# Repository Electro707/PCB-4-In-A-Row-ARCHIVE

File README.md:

# PCB Digital 4-In-A-Row - ARCHIVED

This a PCB is a soldering kit for a 4-In-A-Row game. This specific repo is archived. Previously I didn't use a version manager, and thus I have difference folders for different revs, while now I want to start using git as a version manager (as well as proper releases and stuff). Thus there is a new clean repo for this project, and this is here for archival purposes. 

The new repo can be found here:
[https://github.com/Electro707/PCB-4-In-A-Row](https://github.com/Electro707/PCB-4-In-A-Row)

Rev A1:

Rev A2:

Latest Rev:

## Authors

* **Jamal Bouajjaj** 

## License

See the [LICENSE.md](LICENSE.md) file for details

## Changelog 

What are those version? Well I have documented them under [CHANGELOG.md](CHANGELOG.md).

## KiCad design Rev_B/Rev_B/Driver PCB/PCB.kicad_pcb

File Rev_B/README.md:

## What is these patches??

Before I pushed the project files on GitHub, I had individual folders for each revision. So instead of having those folders uploaded, I decided to make them based on the Rev_B folder as different patches. To get the board, run the following command:

```
cd Rev_B
patch -p0 -t -R -E < ../revb*.patch
```

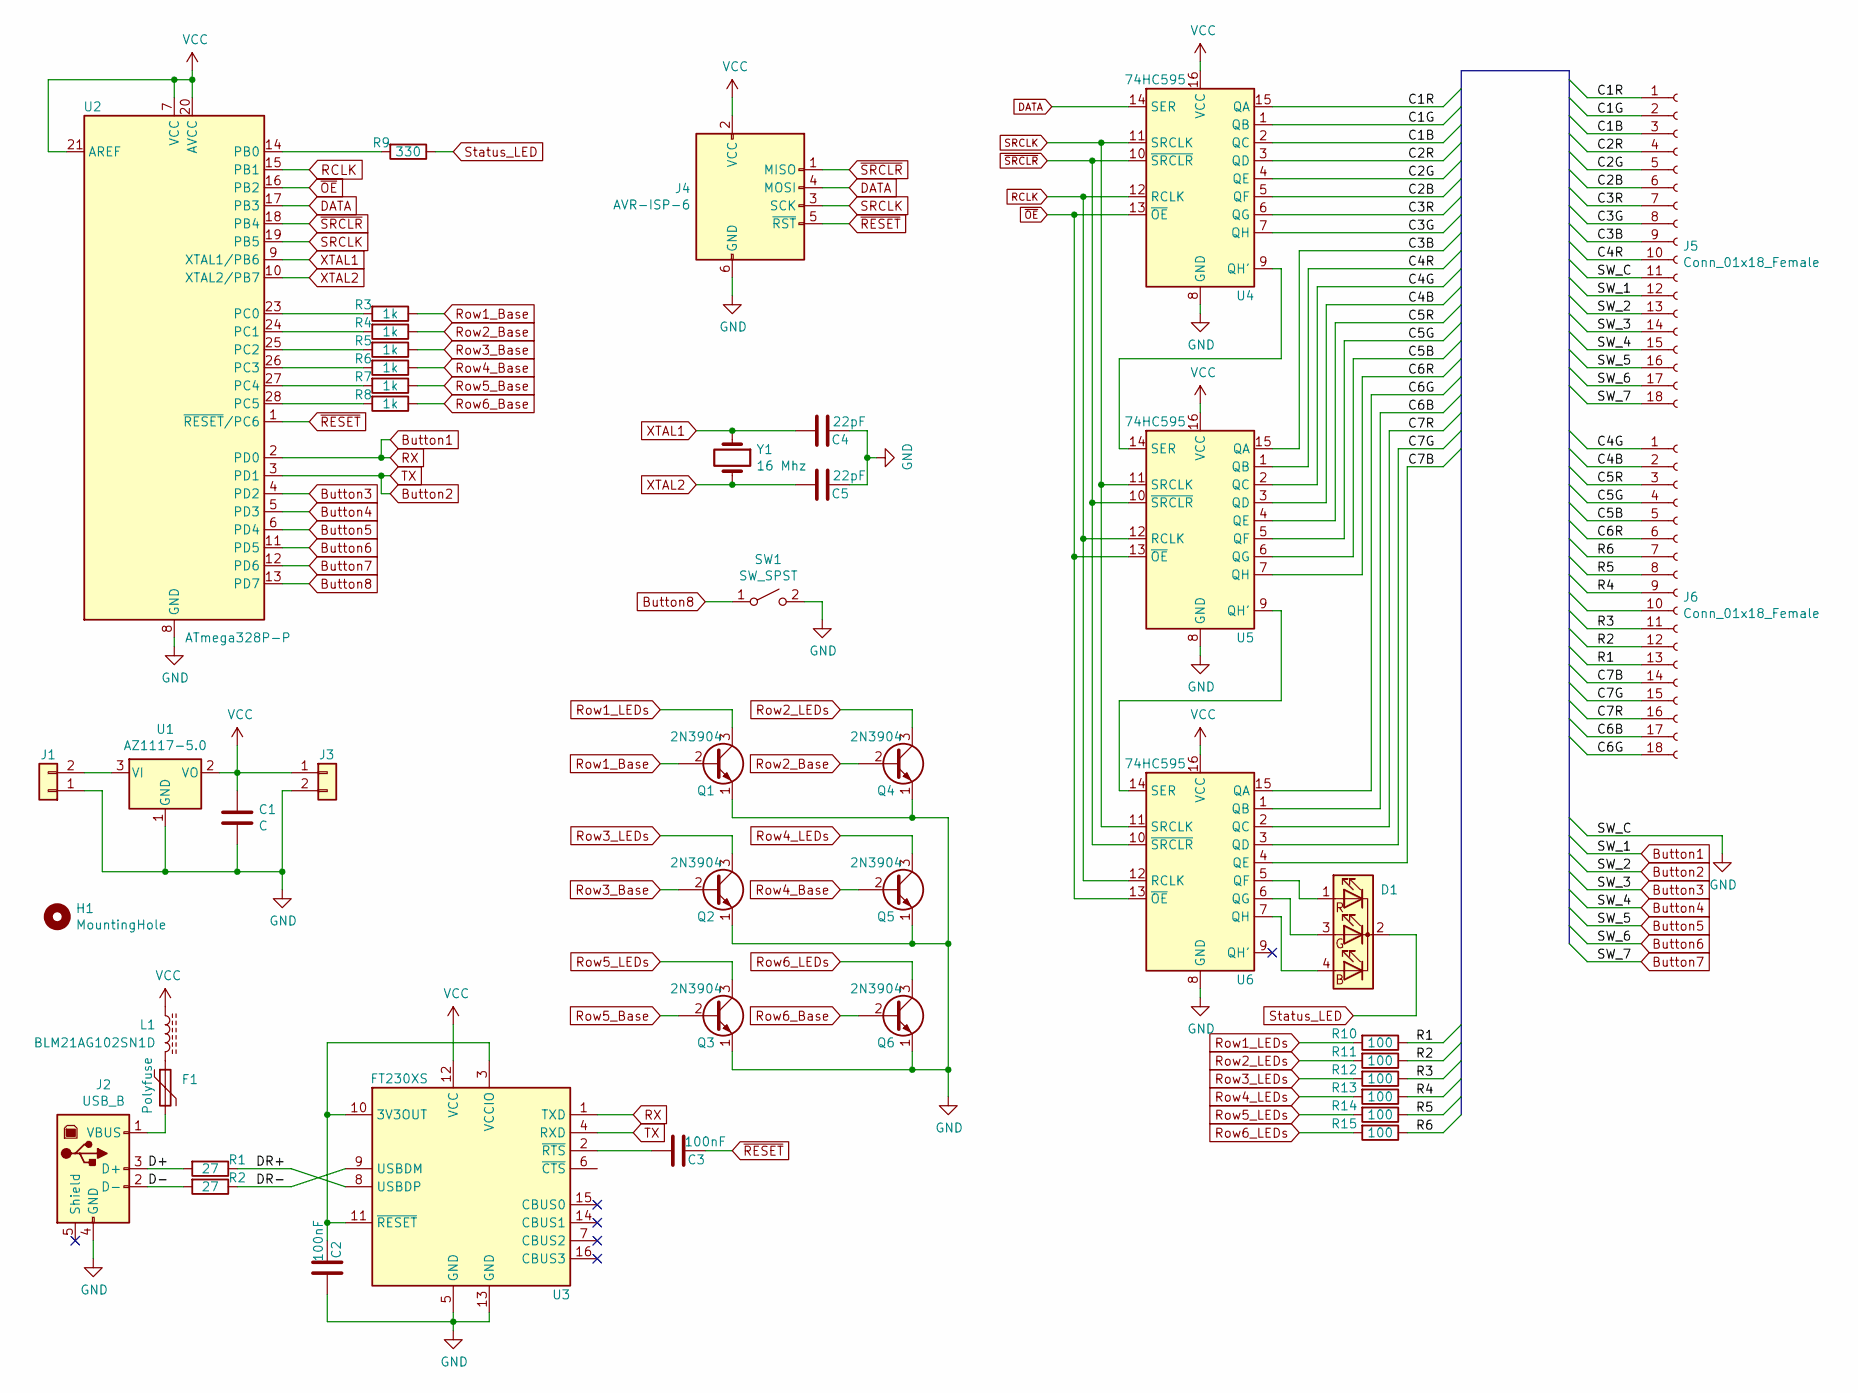
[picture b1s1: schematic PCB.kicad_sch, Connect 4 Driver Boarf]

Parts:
C1: C; C_0805_2012Metric_Pad1.18x1.45mm_HandSolder
C2, C3: 100nF; C_0805_2012Metric_Pad1.18x1.45mm_HandSolder
C4, C5: 22pF; C_Disc_D4.3mm_W1.9mm_P5.00mm
D1: LED_RCGB; LED_D5.0mm-4_RGB_Wide_Pins
F1: Polyfuse; Fuse_1206_3216Metric_Pad1.42x1.75mm_HandSolder
H1: MountingHole; MountingHole_3.2mm_M3_DIN965
J1, J3: Conn_01x02; PinSocket_1x02_P2.54mm_Vertical
J2: USB_B; USB_B_OST_USB-B1HSxx_Horizontal
J4: AVR-ISP-6; PinHeader_2x03_P2.54mm_Horizontal
J5, J6: Conn_01x18_Female; PinSocket_1x18_P2.54mm_Vertical
L1: BLM21AG102SN1D; L_0805_2012Metric_Pad1.15x1.40mm_HandSolder
Q1, Q2, Q3, Q4, Q5, Q6: 2N3904; TO-92_Wide
R1, R2: 27; R_0805_2012Metric_Pad1.20x1.40mm_HandSolder
R3, R4, R5, R6, R7, R8: 1k; R_Axial_DIN0207_L6.3mm_D2.5mm_P10.16mm_Horizontal
R9: 330; R_Axial_DIN0207_L6.3mm_D2.5mm_P10.16mm_Horizontal
R10, R11, R12, R13, R14, R15: 100; R_Axial_DIN0207_L6.3mm_D2.5mm_P10.16mm_Horizontal
SW1: SW_SPST; SW_PUSH_6mm_H5mm
U1: AZ1117-5.0; TO-220-3_Horizontal_TabDown
U2: ATmega328P-P; DIP-28_W7.62mm
U3: FT230XS; SSOP-16_3.9x4.9mm_P0.635mm
U4, U5, U6: 74HC595; DIP-16_W7.62mm_LongPads
Y1: 16 Mhz; Crystal_HC49-4H_Vertical

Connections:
/C1B: J5.3, U4.2 (QC)
/C1G: J5.2, U4.1 (QB)
/C1R: J5.1, U4.15 (QA)
/C2B: J5.6, U4.5 (QF)
/C2G: J5.5, U4.4 (QE)
/C2R: J5.4, U4.3 (QD)
/C3B: J5.9, U5.15 (QA)
/C3G: J5.8, U4.7 (QH)
/C3R: J5.7, U4.6 (QG)
/C4B: J6.2, U5.3 (QD)
/C4G: J6.1, U5.2 (QC)
/C4R: J5.10, U5.1 (QB)
/C5B: J6.5, U5.6 (QG)
/C5G: J6.4, U5.5 (QF)
/C5R: J6.3, U5.4 (QE)
/C6B: J6.17, U6.1 (QB)
/C6G: J6.18, U6.15 (QA)
/C6R: J6.6, U5.7 (QH)
/C7B: J6.14, U6.4 (QE)
/C7G: J6.15, U6.3 (QD)
/C7R: J6.16, U6.2 (QC)
/D+: J2.3 (D+), R1.2
/D-: J2.2 (D-), R2.2
/DR+: R1.1, U3.8 (USBDP)
/DR-: R2.1, U3.9 (USBDM)
/R1: J6.13, R10.1
/R2: J6.12, R11.1
/R3: J6.11, R12.1
/R4: J6.9, R13.1
/R5: J6.8, R14.1
/R6: J6.7, R15.1
Button1: J5.12, U2.2 (PD0), U3.1 (TXD)
Button2: J5.13, U2.3 (PD1), U3.4 (RXD)
Button3: J5.14, U2.4 (PD2)
Button4: J5.15, U2.5 (PD3)
Button5: J5.16, U2.6 (PD4)
Button6: J5.17, U2.11 (PD5)
Button7: J5.18, U2.12 (PD6)
Button8: SW1.1 (A), U2.13 (PD7)
DATA: J4.4 (MOSI), U2.17 (PB3), U4.14 (SER)
GND: C1.2, C2.2, C4.1, C5.1, J1.1, J2.4 (GND), J3.2, J4.6 (GND), J5.11, Q1.1 (E), Q2.1 (E), Q3.1 (E), Q4.1 (E), Q5.1 (E), Q6.1 (E), SW1.2 (B), U1.1 (GND), U2.8 (GND), U2.22 (GND), U3.5 (GND), U3.13 (GND), U4.8 (GND), U5.8 (GND), U6.8 (GND)
unnamed: C2.1, U3.3 (VCCIO), U3.10 (3V3OUT), U3.11 (~RESET)
unnamed: C3.2, U3.2 (~RTS)
unnamed: D1.1 (RA), U6.5 (QF)
unnamed: D1.3 (GA), U6.6 (QG)
unnamed: D1.4 (BA), U6.7 (QH)
unnamed: F1.1, L1.2
unnamed: F1.2, J2.1 (VBUS)
unnamed: J1.2, U1.3 (VI)
unnamed: R3.2, U2.23 (PC0)
unnamed: R4.2, U2.24 (PC1)
unnamed: R5.2, U2.25 (PC2)
unnamed: R6.2, U2.26 (PC3)
unnamed: R7.2, U2.27 (PC4)
unnamed: R8.2, U2.28 (PC5)
unnamed: R9.2, U2.14 (PB0)
unnamed: U4.9 (QH'), U5.14 (SER)
unnamed: U5.9 (QH'), U6.14 (SER)
RCLK: U2.15 (PB1), U4.12 (RCLK), U5.12 (RCLK), U6.12 (RCLK)
Row1_Base: Q1.2 (B), R3.1
Row1_LEDs: Q1.3 (C), R10.2
Row2_Base: Q4.2 (B), R4.1
Row2_LEDs: Q4.3 (C), R11.2
Row3_Base: Q2.2 (B), R5.1
Row3_LEDs: Q2.3 (C), R12.2
Row4_Base: Q5.2 (B), R6.1
Row4_LEDs: Q5.3 (C), R13.2
Row5_Base: Q3.2 (B), R7.1
Row5_LEDs: Q3.3 (C), R14.2
Row6_Base: Q6.2 (B), R8.1
Row6_LEDs: Q6.3 (C), R15.2
SRCLK: J4.3 (SCK), U2.19 (PB5), U4.11 (SRCLK), U5.11 (SRCLK), U6.11 (SRCLK)
Status_LED: D1.2 (K), R9.1
VCC: C1.1, J3.1, J4.2 (VCC), L1.1, U1.2 (VO), U2.7 (VCC), U2.20 (AVCC), U2.21 (AREF), U3.12 (VCC), U4.16 (VCC), U5.16 (VCC), U6.16 (VCC)
XTAL1: C4.2, U2.9 (XTAL1/PB6), Y1.1
XTAL2: C5.2, U2.10 (XTAL2/PB7), Y1.2
~OE: U2.16 (PB2), U4.13 (~OE), U5.13 (~OE), U6.13 (~OE)
~RESET: C3.1, J4.5 (~RST), U2.1 (~RESET~/PC6)
~SRCLR: J4.1 (MISO), U2.18 (PB4), U4.10 (~SRCLR), U5.10 (~SRCLR), U6.10 (~SRCLR)

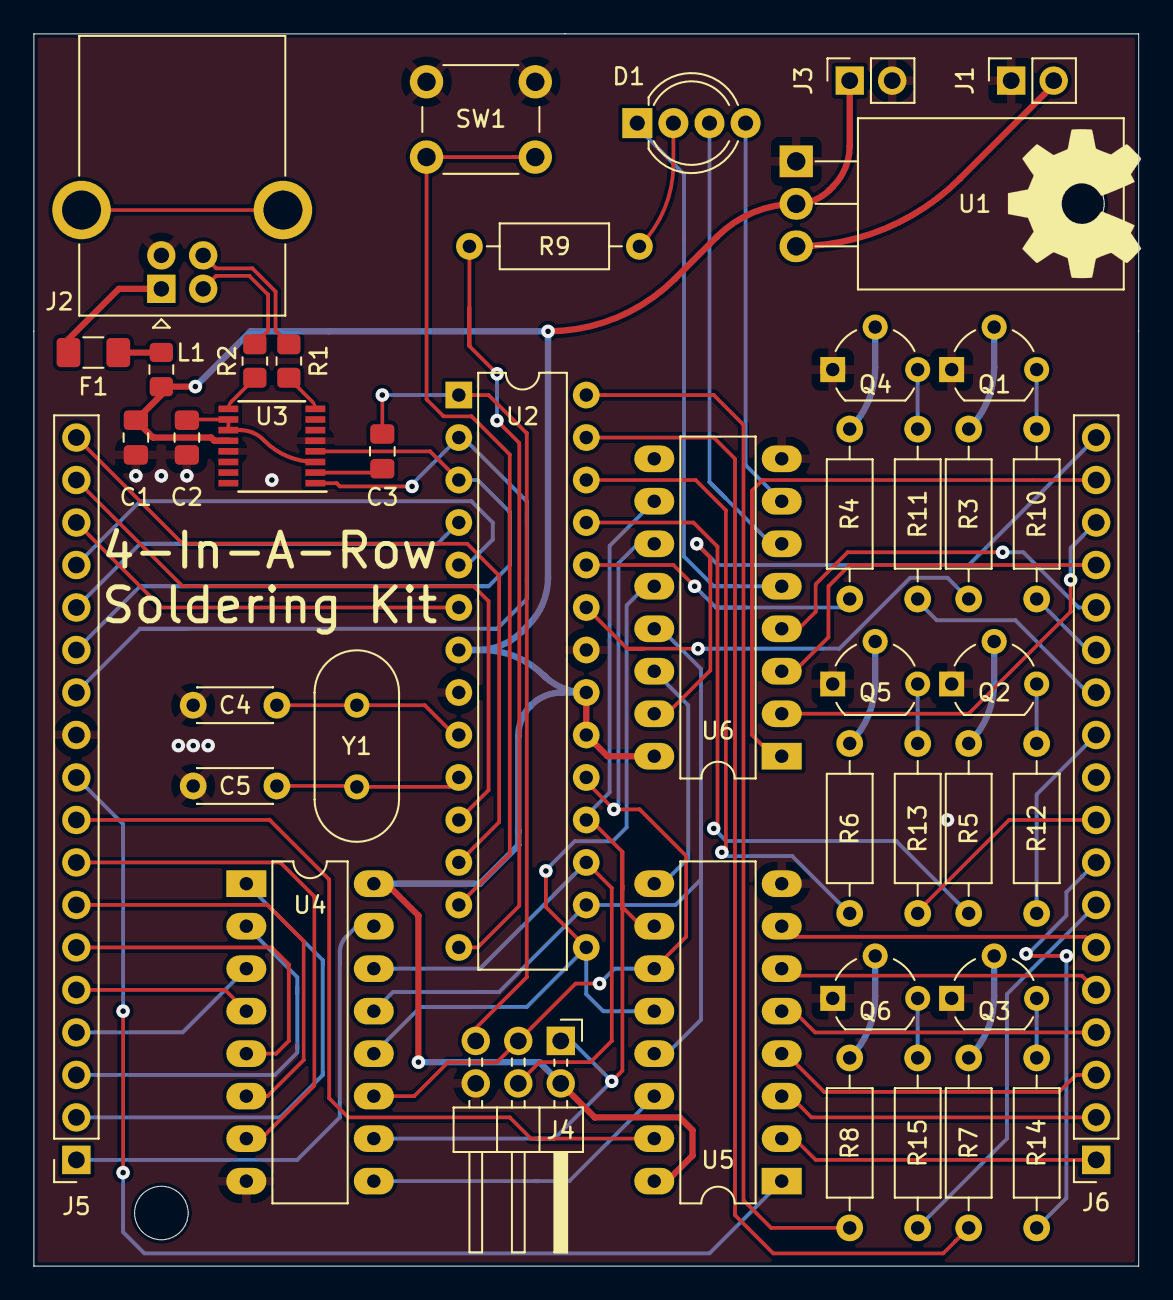
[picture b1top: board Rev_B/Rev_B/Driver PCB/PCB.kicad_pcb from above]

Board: 2 copper layers, 66.0 x 73.7 mm, 44 parts (0 on the bottom side), 79 nets.

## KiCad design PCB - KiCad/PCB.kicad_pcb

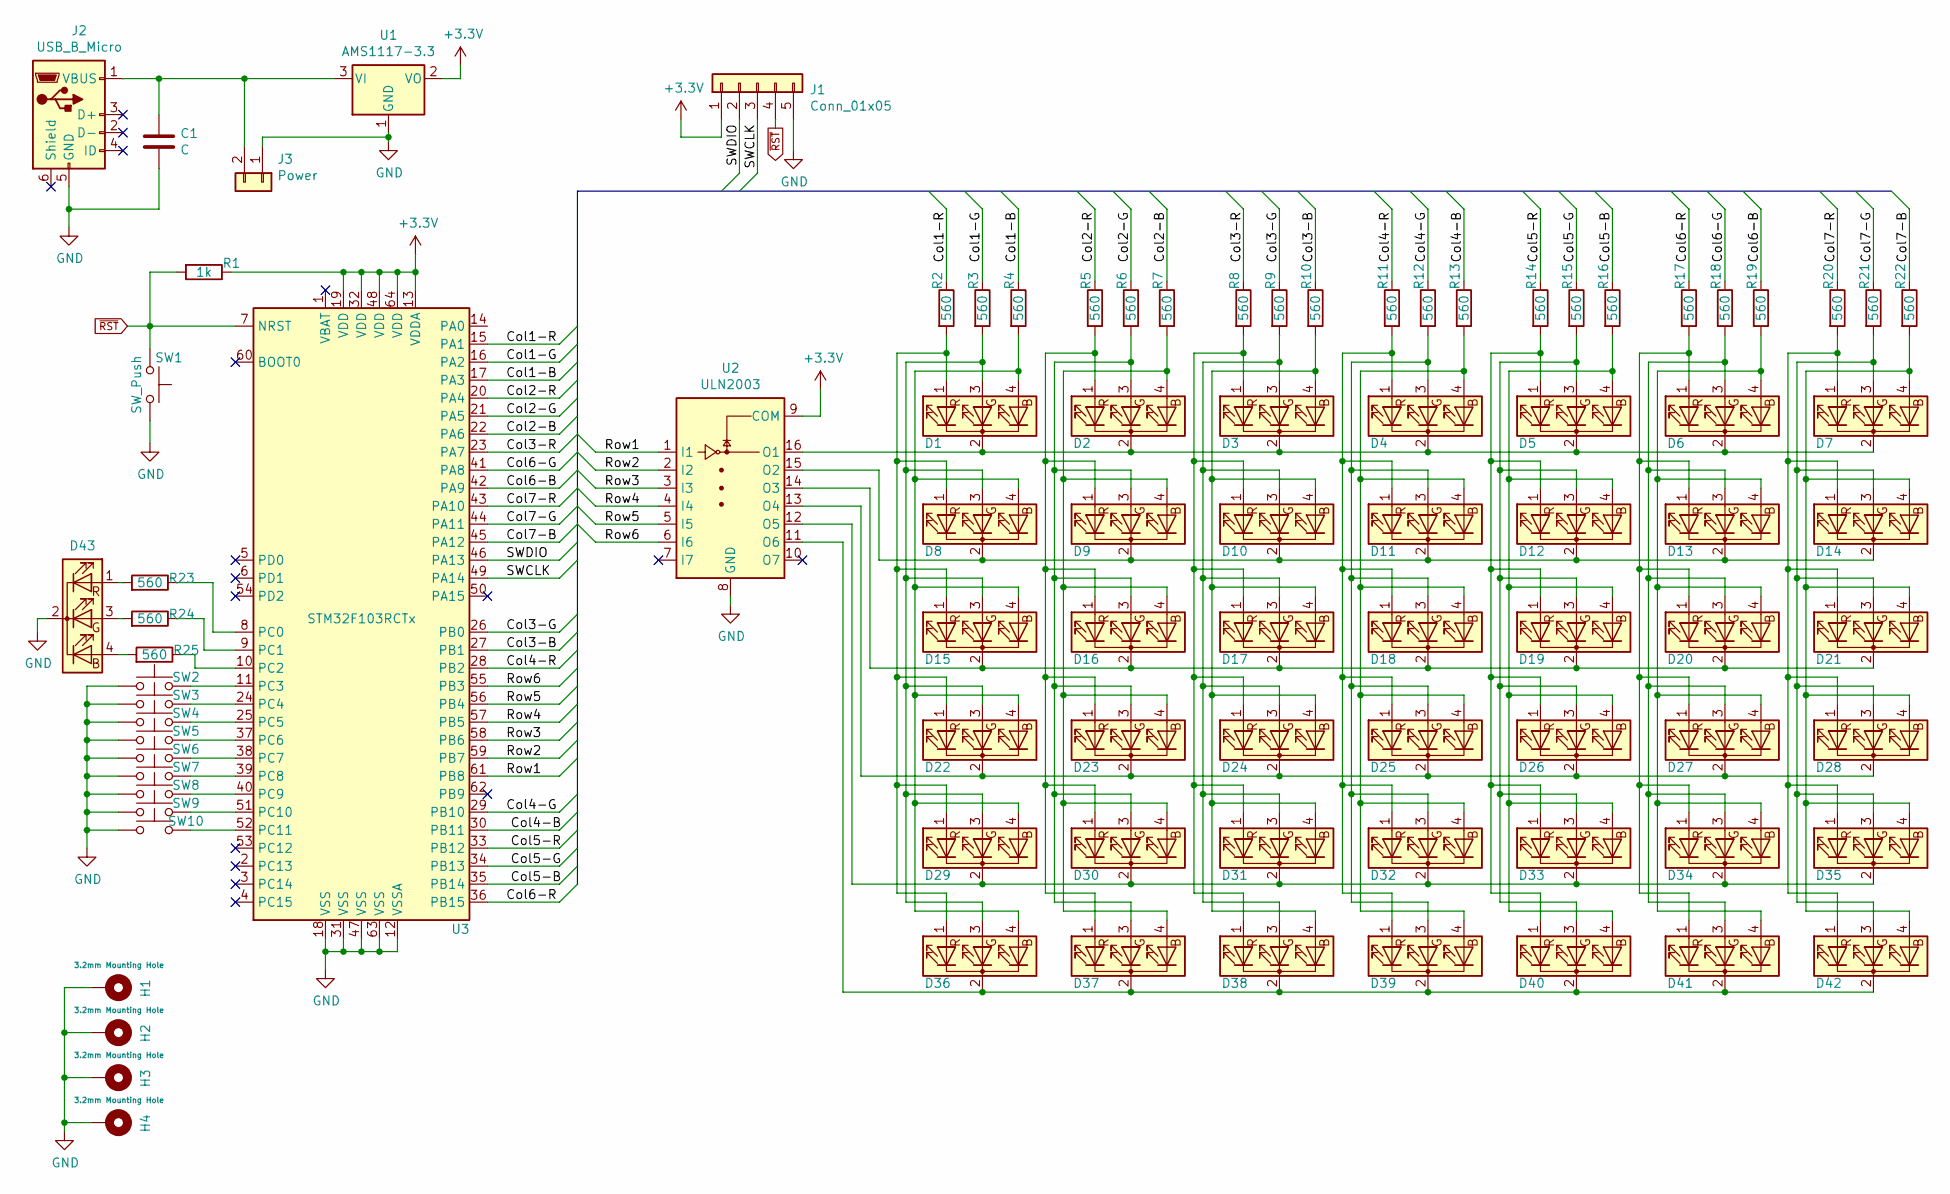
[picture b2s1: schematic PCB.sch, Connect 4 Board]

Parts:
C1: C; C_0805_2012Metric_Pad1.15x1.40mm_HandSolder
D1, D2, D3, D4, D5, D6, D7, D8, D9, D10, D11, D12, D13, D14, D15, D16, D17, D18, D19, D20, D21, D22, D23, D24, D25, D26, D27, D28, D29, D30, D31, D32, D33, D34, D35, D36, D37, D38, D39, D40, D41, D42, D43: LED_RCGB; LED_D5.0mm-4_RGB
H1, H2, H3, H4: 3.2mm Mounting Hole; MountingHole_3.2mm_M3
J1: Conn_01x05; PinHeader_1x05_P2.54mm_Vertical
J2: USB_B_Micro; USB_Micro-B_Molex_47346-0001
J3: Power; PinHeader_1x02_P2.54mm_Vertical
R1: 1k; R_0805_2012Metric_Pad1.15x1.40mm_HandSolder
R2, R3, R4, R5, R6, R7, R8, R9, R10, R11, R12, R13, R14, R15, R16, R17, R18, R19, R20, R21, R22, R23, R24, R25: 560; R_0805_2012Metric_Pad1.15x1.40mm_HandSolder
SW1: SW_Push; SW_SPST_PTS810
SW2, SW3, SW4, SW5, SW6, SW7, SW8, SW9, SW10: SW_Push; SW_PUSH_6mm_H5mm
U1: AMS1117-3.3; SOT-223-3_TabPin2
U2: ULN2003; SOP-16_4.55x10.3mm_P1.27mm
U3: STM32F103RCTx; LQFP-64_10x10mm_P0.5mm

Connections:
+3V3: J1.1, R1.1, U1.2 (VO), U2.9 (COM), U3.13 (VDDA), U3.19 (VDD), U3.32 (VDD), U3.48 (VDD), U3.64 (VDD)
/Col1-B: R4.1, U3.17 (PA3)
/Col1-G: R3.1, U3.16 (PA2)
/Col1-R: R2.1, U3.15 (PA1)
/Col2-B: R7.1, U3.22 (PA6)
/Col2-G: R6.1, U3.21 (PA5)
/Col2-R: R5.1, U3.20 (PA4)
/Col3-B: R10.1, U3.27 (PB1)
/Col3-G: R9.1, U3.26 (PB0)
/Col3-R: R8.1, U3.23 (PA7)
/Col4-B: R13.1, U3.30 (PB11)
/Col4-G: R12.1, U3.29 (PB10)
/Col4-R: R11.1, U3.28 (PB2)
/Col5-B: R16.1, U3.35 (PB14)
/Col5-G: R15.1, U3.34 (PB13)
/Col5-R: R14.1, U3.33 (PB12)
/Col6-B: R19.1, U3.42 (PA9)
/Col6-G: R18.1, U3.41 (PA8)
/Col6-R: R17.1, U3.36 (PB15)
/Col7-B: R22.1, U3.45 (PA12)
/Col7-G: R21.1, U3.44 (PA11)
/Col7-R: R20.1, U3.43 (PA10)
/Row1: U2.1 (I1), U3.61 (PB8)
/Row2: U2.2 (I2), U3.59 (PB7)
/Row3: U2.3 (I3), U3.58 (PB6)
/Row4: U2.4 (I4), U3.57 (PB5)
/Row5: U2.5 (I5), U3.56 (PB4)
/Row6: U2.6 (I6), U3.55 (PB3)
/SWCLK: J1.3, U3.49 (PA14)
/SWDIO: J1.2, U3.46 (PA13)
GND: C1.2, D43.2 (K), H1.1, H2.1, H3.1, H4.1, J1.5, J2.5 (GND), J3.1, SW1.2, SW2.1, SW3.1, SW4.1, SW5.1, SW6.1, SW7.1, SW8.1, SW9.1, SW10.1, U1.1 (GND), U2.8 (GND), U3.12 (VSSA), U3.18 (VSS), U3.31 (VSS), U3.47 (VSS), U3.63 (VSS)
unnamed: C1.1, J2.1 (VBUS), J3.2, U1.3 (VI)
unnamed: D1.1 (RA), D8.1 (RA), D15.1 (RA), D22.1 (RA), D29.1 (RA), D36.1 (RA), R2.2
unnamed: D1.2 (K), D2.2 (K), D3.2 (K), D4.2 (K), D5.2 (K), D6.2 (K), D7.2 (K), U2.16 (O1)
unnamed: D1.3 (GA), D8.3 (GA), D15.3 (GA), D22.3 (GA), D29.3 (GA), D36.3 (GA), R3.2
unnamed: D1.4 (BA), D8.4 (BA), D15.4 (BA), D22.4 (BA), D29.4 (BA), D36.4 (BA), R4.2
unnamed: D3.1 (RA), D10.1 (RA), D17.1 (RA), D24.1 (RA), D31.1 (RA), D38.1 (RA), R8.2
unnamed: D8.2 (K), D9.2 (K), D10.2 (K), D11.2 (K), D12.2 (K), D13.2 (K), D14.2 (K), U2.15 (O2)
unnamed: D3.3 (GA), D10.3 (GA), D17.3 (GA), D24.3 (GA), D31.3 (GA), D38.3 (GA), R9.2
unnamed: D3.4 (BA), D10.4 (BA), D17.4 (BA), D24.4 (BA), D31.4 (BA), D38.4 (BA), R10.2
unnamed: D4.1 (RA), D11.1 (RA), D18.1 (RA), D25.1 (RA), D32.1 (RA), D39.1 (RA), R11.2
unnamed: D4.3 (GA), D11.3 (GA), D18.3 (GA), D25.3 (GA), D32.3 (GA), D39.3 (GA), R12.2
unnamed: D4.4 (BA), D11.4 (BA), D18.4 (BA), D25.4 (BA), D32.4 (BA), D39.4 (BA), R13.2
unnamed: D5.1 (RA), D12.1 (RA), D19.1 (RA), D26.1 (RA), D33.1 (RA), D40.1 (RA), R14.2
unnamed: D5.3 (GA), D12.3 (GA), D19.3 (GA), D26.3 (GA), D33.3 (GA), D40.3 (GA), R15.2
unnamed: D5.4 (BA), D12.4 (BA), D19.4 (BA), D26.4 (BA), D33.4 (BA), D40.4 (BA), R16.2
unnamed: D6.1 (RA), D13.1 (RA), D20.1 (RA), D27.1 (RA), D34.1 (RA), D41.1 (RA), R17.2
unnamed: D6.3 (GA), D13.3 (GA), D20.3 (GA), D27.3 (GA), D34.3 (GA), D41.3 (GA), R18.2
unnamed: D6.4 (BA), D13.4 (BA), D20.4 (BA), D27.4 (BA), D34.4 (BA), D41.4 (BA), R19.2
unnamed: D7.1 (RA), D14.1 (RA), D21.1 (RA), D28.1 (RA), D35.1 (RA), D42.1 (RA), R20.2
unnamed: D7.3 (GA), D14.3 (GA), D21.3 (GA), D28.3 (GA), D35.3 (GA), D42.3 (GA), R21.2
unnamed: D7.4 (BA), D14.4 (BA), D21.4 (BA), D28.4 (BA), D35.4 (BA), D42.4 (BA), R22.2
unnamed: D15.2 (K), D16.2 (K), D17.2 (K), D18.2 (K), D19.2 (K), D20.2 (K), D21.2 (K), U2.14 (O3)
unnamed: D2.1 (RA), D9.1 (RA), D16.1 (RA), D23.1 (RA), D30.1 (RA), D37.1 (RA), R5.2
unnamed: D2.3 (GA), D9.3 (GA), D16.3 (GA), D23.3 (GA), D30.3 (GA), D37.3 (GA), R6.2
unnamed: D2.4 (BA), D9.4 (BA), D16.4 (BA), D23.4 (BA), D30.4 (BA), D37.4 (BA), R7.2
unnamed: D22.2 (K), D23.2 (K), D24.2 (K), D25.2 (K), D26.2 (K), D27.2 (K), D28.2 (K), U2.13 (O4)
unnamed: D29.2 (K), D30.2 (K), D31.2 (K), D32.2 (K), D33.2 (K), D34.2 (K), D35.2 (K), U2.12 (O5)
unnamed: D36.2 (K), D37.2 (K), D38.2 (K), D39.2 (K), D40.2 (K), D41.2 (K), D42.2 (K), U2.11 (O6)
unnamed: D43.1 (RA), R23.2
unnamed: D43.3 (GA), R24.2
unnamed: D43.4 (BA), R25.2
unnamed: R23.1, U3.8 (PC0)
unnamed: R24.1, U3.9 (PC1)
unnamed: R25.1, U3.10 (PC2)
unnamed: SW2.2, U3.11 (PC3)
unnamed: SW3.2, U3.24 (PC4)
unnamed: SW4.2, U3.25 (PC5)
unnamed: SW5.2, U3.37 (PC6)
unnamed: SW6.2, U3.38 (PC7)
unnamed: SW7.2, U3.39 (PC8)
unnamed: SW8.2, U3.40 (PC9)
unnamed: SW9.2, U3.51 (PC10)
unnamed: SW10.2, U3.52 (PC11)
~RST: J1.4, R1.2, SW1.1, U3.7 (NRST)

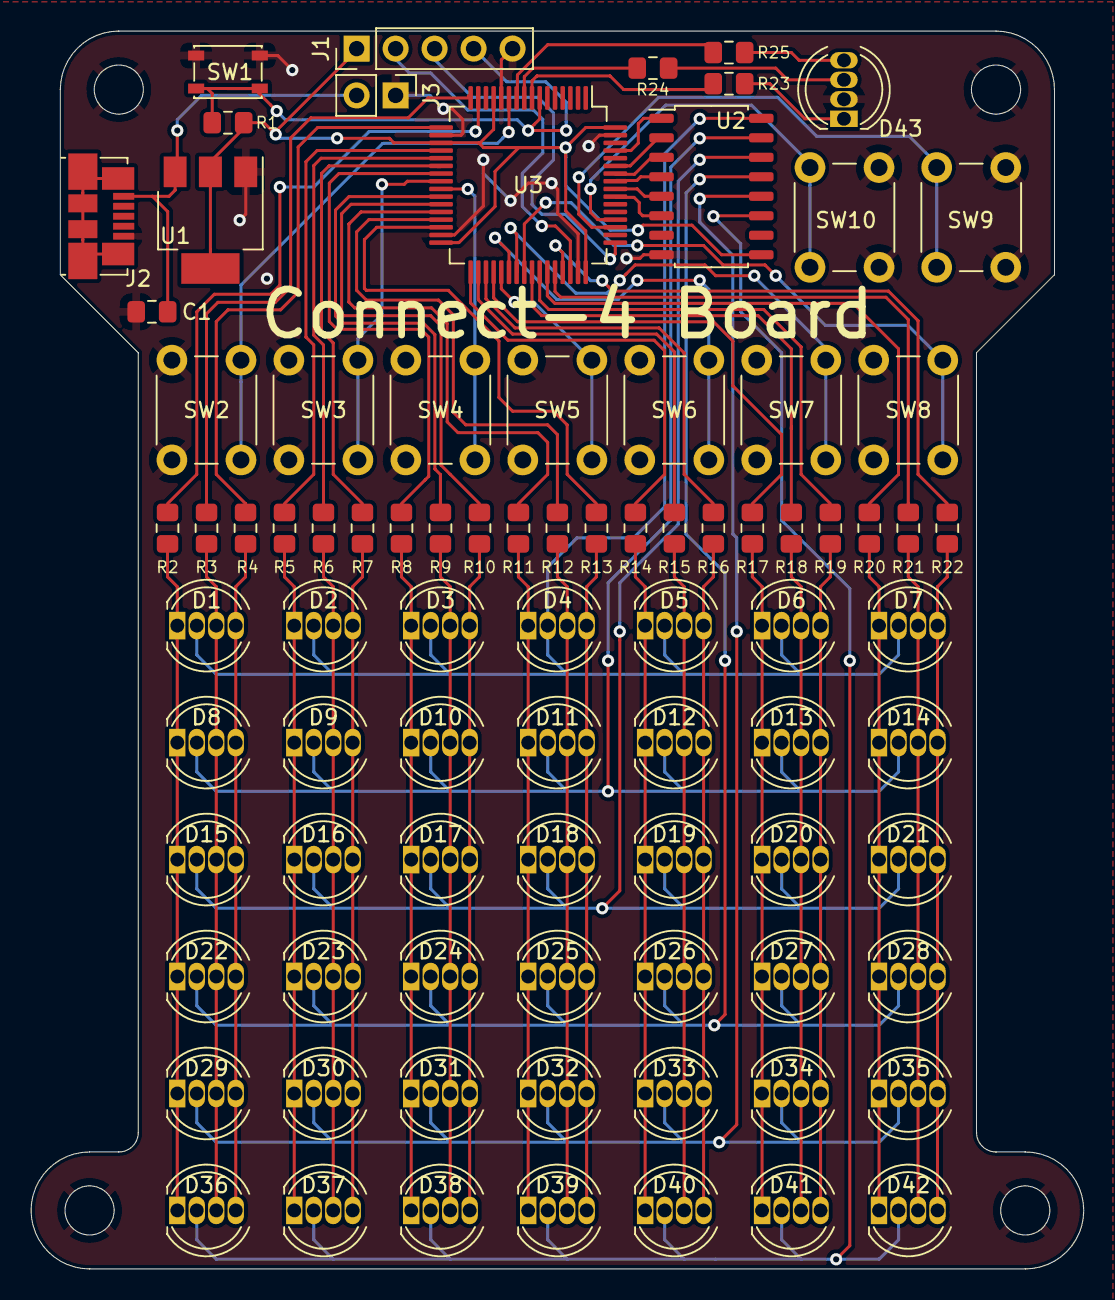
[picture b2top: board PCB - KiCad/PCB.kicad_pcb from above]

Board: 2 copper layers, 68.6 x 80.6 mm, 89 parts (0 on the bottom side), 75 nets.

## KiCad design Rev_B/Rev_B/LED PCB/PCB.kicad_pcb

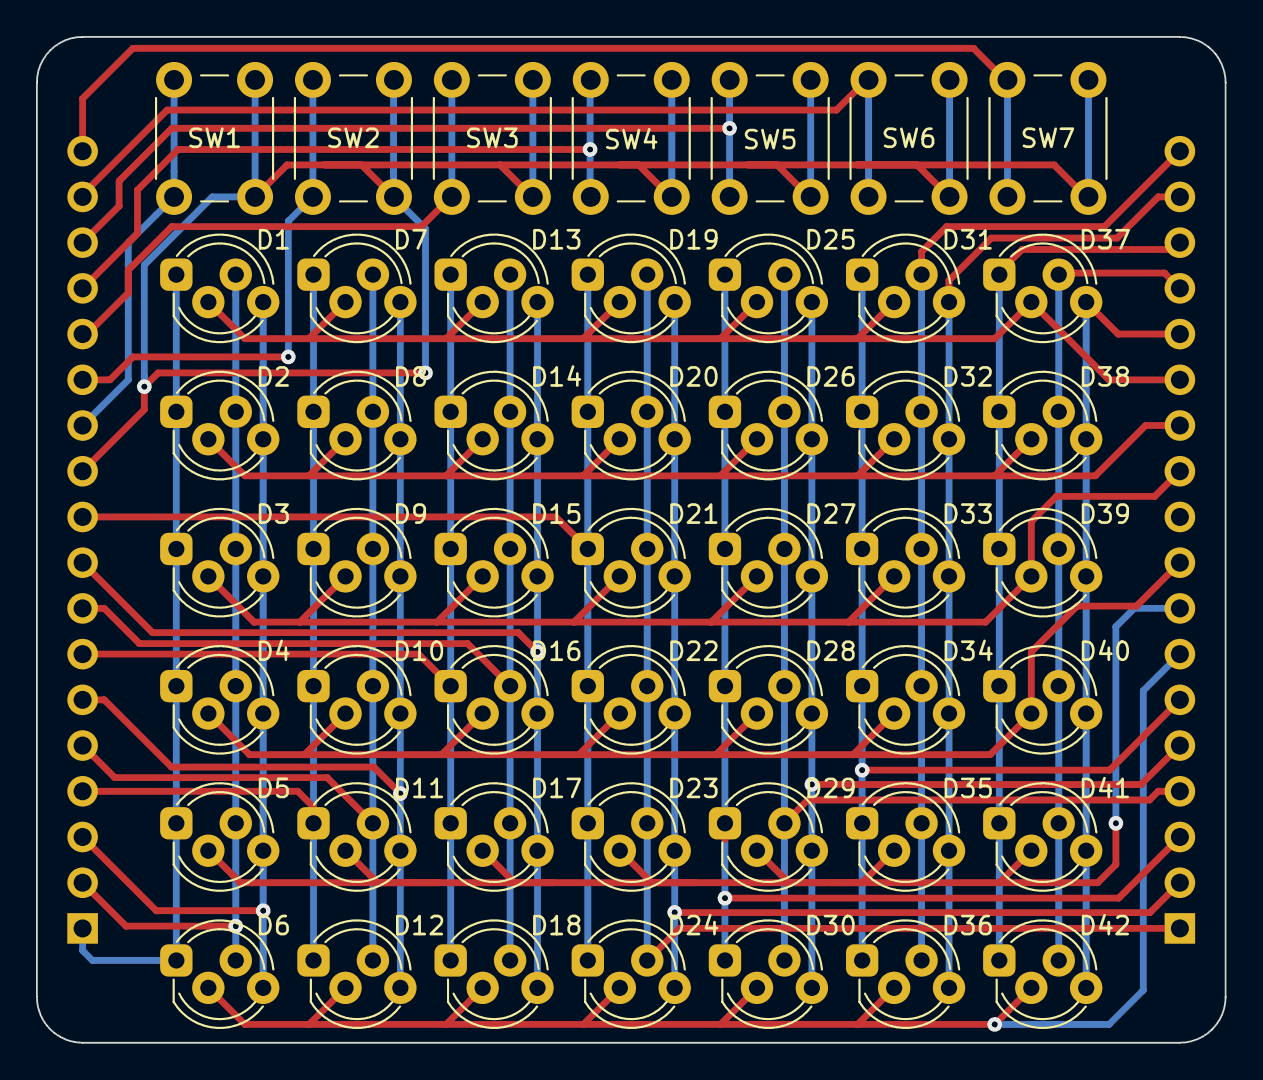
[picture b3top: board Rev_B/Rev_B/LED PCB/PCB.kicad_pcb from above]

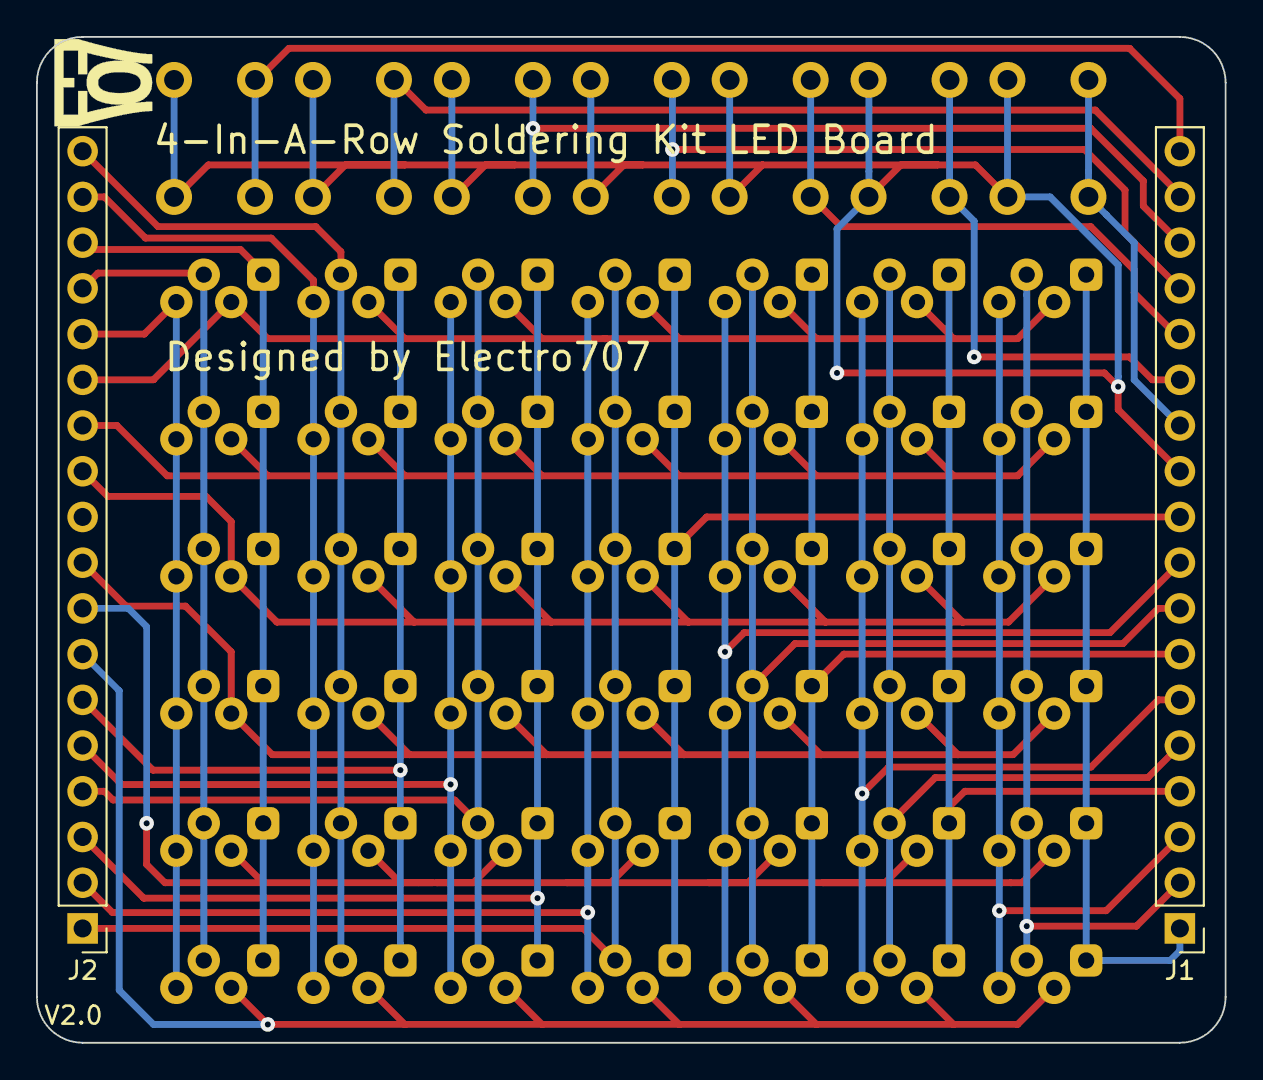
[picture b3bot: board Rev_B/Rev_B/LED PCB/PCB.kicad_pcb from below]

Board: 2 copper layers, 66.0 x 55.9 mm, 51 parts (2 on the bottom side), 35 nets.

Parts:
D1, D2, D3, D4, D5, D6, D7, D8, D9, D10, D11, D12, D13, D14, D15, D16, D17, D18, D19, D20, D21, D22, D23, D24, D25, D26, D27, D28, D29, D30, D31, D32, D33, D34, D35, D36, D37, D38, D39, D40, D41, D42: LED_RCGB; LED_D5.0mm-4_RGB_Staggered_Pins
J1, J2: Conn_01x18_Male; PinHeader_1x18_P2.54mm_Vertical
SW1, SW2, SW3, SW4, SW5, SW6, SW7: SW_Push; SW_PUSH_6mm_H8mm

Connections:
/C1B: D1.4 (BA), D2.4 (BA), D3.4 (BA), D4.4 (BA), D5.4 (BA), D6.4 (BA), J1.3
/C1G: D1.3 (GA), D2.3 (GA), D3.3 (GA), D4.3 (GA), D5.3 (GA), D6.3 (GA), J1.2
/C1R: D1.1 (RA), D2.1 (RA), D3.1 (RA), D4.1 (RA), D5.1 (RA), D6.1 (RA), J1.1
/C2B: D7.4 (BA), D8.4 (BA), D9.4 (BA), D10.4 (BA), D11.4 (BA), D12.4 (BA), J1.6
/C2G: D7.3 (GA), D8.3 (GA), D9.3 (GA), D10.3 (GA), D11.3 (GA), D12.3 (GA), J1.5
/C2R: D7.1 (RA), D8.1 (RA), D9.1 (RA), D10.1 (RA), D11.1 (RA), D12.1 (RA), J1.4
/C3B: D13.4 (BA), D14.4 (BA), D15.4 (BA), D16.4 (BA), D17.4 (BA), D18.4 (BA), J1.9
/C3G: D13.3 (GA), D14.3 (GA), D15.3 (GA), D16.3 (GA), D17.3 (GA), D18.3 (GA), J1.8
/C3R: D13.1 (RA), D14.1 (RA), D15.1 (RA), D16.1 (RA), D17.1 (RA), D18.1 (RA), J1.7
/C4B: D19.4 (BA), D20.4 (BA), D21.4 (BA), D22.4 (BA), D23.4 (BA), D24.4 (BA), J2.2
/C4G: D19.3 (GA), D20.3 (GA), D21.3 (GA), D22.3 (GA), D23.3 (GA), D24.3 (GA), J2.1
/C4R: D19.1 (RA), D20.1 (RA), D21.1 (RA), D22.1 (RA), D23.1 (RA), D24.1 (RA), J1.10
/C5B: D25.4 (BA), D26.4 (BA), D27.4 (BA), D28.4 (BA), D29.4 (BA), D30.4 (BA), J2.5
/C5G: D25.3 (GA), D26.3 (GA), D27.3 (GA), D28.3 (GA), D29.3 (GA), D30.3 (GA), J2.4
/C5R: D25.1 (RA), D26.1 (RA), D27.1 (RA), D28.1 (RA), D29.1 (RA), D30.1 (RA), J2.3
/C6B: D31.4 (BA), D32.4 (BA), D33.4 (BA), D34.4 (BA), D35.4 (BA), D36.4 (BA), J2.17
/C6G: D31.3 (GA), D32.3 (GA), D33.3 (GA), D34.3 (GA), D35.3 (GA), D36.3 (GA), J2.18
/C6R: D31.1 (RA), D32.1 (RA), D33.1 (RA), D34.1 (RA), D35.1 (RA), D36.1 (RA), J2.6
/C7B: D37.4 (BA), D38.4 (BA), D39.4 (BA), D40.4 (BA), D41.4 (BA), D42.4 (BA), J2.14
/C7G: D37.3 (GA), D38.3 (GA), D39.3 (GA), D40.3 (GA), D41.3 (GA), D42.3 (GA), J2.15
/C7R: D37.1 (RA), D38.1 (RA), D39.1 (RA), D40.1 (RA), D41.1 (RA), D42.1 (RA), J2.16
/R1: D1.2 (K), D7.2 (K), D13.2 (K), D19.2 (K), D25.2 (K), D31.2 (K), D37.2 (K), J2.13
/R2: D2.2 (K), D8.2 (K), D14.2 (K), D20.2 (K), D26.2 (K), D32.2 (K), D38.2 (K), J2.12
/R3: D3.2 (K), D9.2 (K), D15.2 (K), D21.2 (K), D27.2 (K), D33.2 (K), D39.2 (K), J2.11
/R4: D4.2 (K), D10.2 (K), D16.2 (K), D22.2 (K), D28.2 (K), D34.2 (K), D40.2 (K), J2.9
/R5: D5.2 (K), D11.2 (K), D17.2 (K), D23.2 (K), D29.2 (K), D35.2 (K), D41.2 (K), J2.8
/R6: D6.2 (K), D12.2 (K), D18.2 (K), D24.2 (K), D30.2 (K), D36.2 (K), D42.2 (K), J2.7
/SW_1: J1.12, SW1.1
/SW_2: J1.13, SW2.1
/SW_3: J1.14, SW3.1
/SW_4: J1.15, SW4.1
/SW_5: J1.16, SW5.1
/SW_6: J1.17, SW6.1
/SW_7: J1.18, SW7.1
/SW_C: J1.11, SW1.2, SW2.2, SW3.2, SW4.2, SW5.2, SW6.2, SW7.2

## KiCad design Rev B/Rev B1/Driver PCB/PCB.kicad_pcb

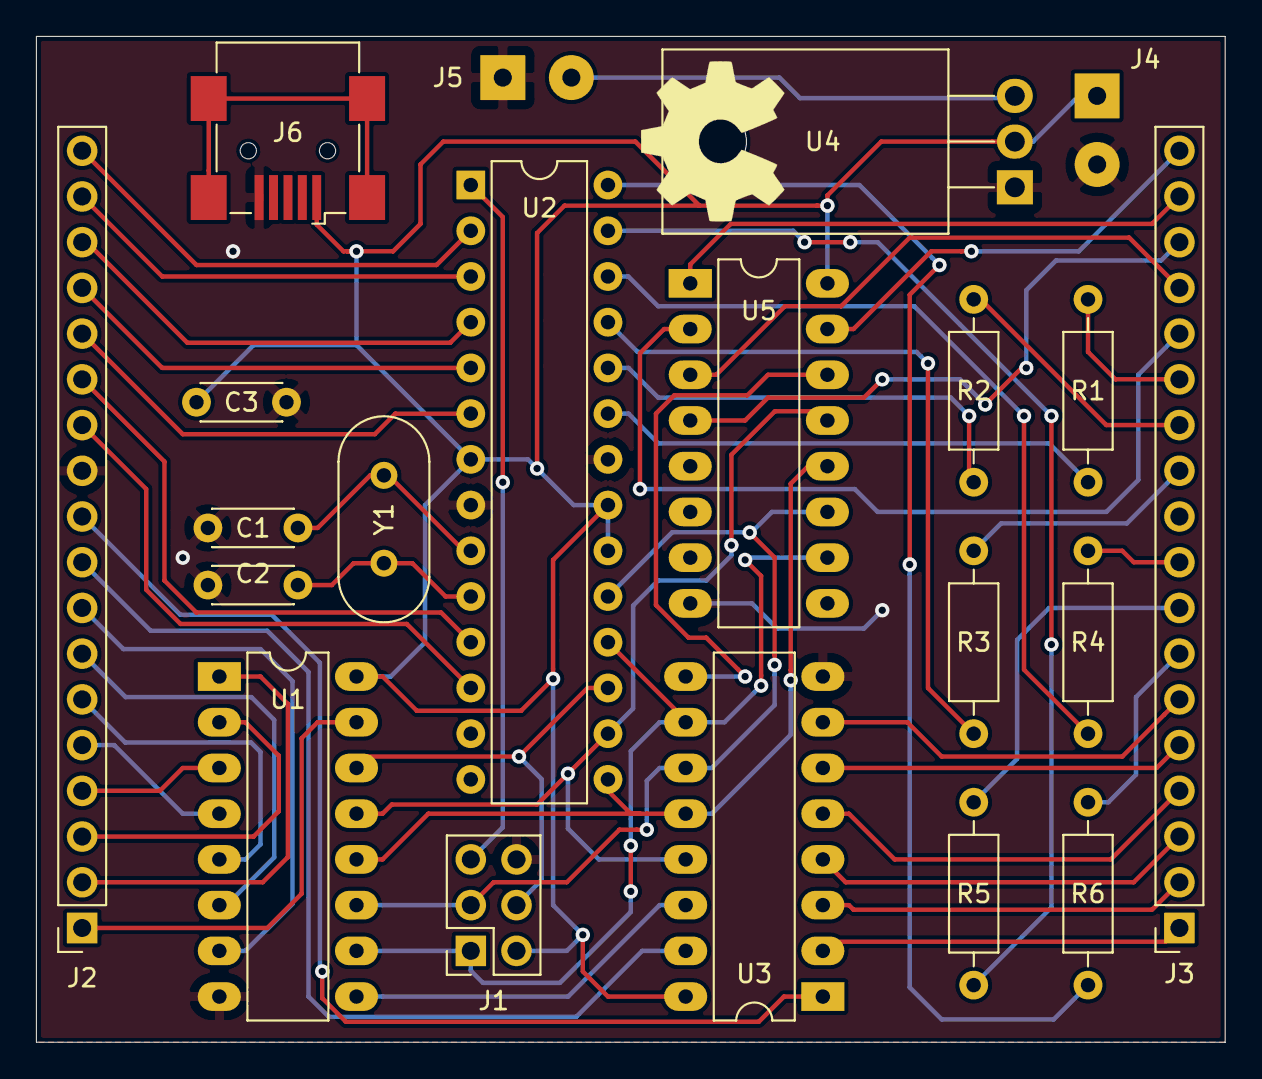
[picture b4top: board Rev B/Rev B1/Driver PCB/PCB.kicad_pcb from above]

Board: 2 copper layers, 66.0 x 55.9 mm, 21 parts (0 on the bottom side), 53 nets.

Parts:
C1, C2, C3: C; C_Disc_D4.3mm_W1.9mm_P5.00mm
J1: Conn_02x03_Odd_Even; PinSocket_2x03_P2.54mm_Vertical
J2, J3: Conn_01x18_Female; PinSocket_1x18_P2.54mm_Vertical
J4, J5: Conn_01x02; SolderWirePad_1x02_P3.81mm_Drill1mm
J6: USB_B_Mini; USB_Mini-B_Wuerth_65100516121_Horizontal
R1, R2, R3, R4, R5, R6: R; R_Axial_DIN0207_L6.3mm_D2.5mm_P10.16mm_Horizontal
U1, U3, U5: 74HC595; DIP-16_W7.62mm_LongPads
U2: ATmega328P-PU; DIP-28_W7.62mm
U4: AZ1117-5.0; TO-220-3_Horizontal_TabDown
Y1: 16 Mhz; Crystal_HC49-4H_Vertical

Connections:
/C1B: J2.3, U1.2
/C1G: J2.2, U1.1
/C1R: J2.1, U1.15
/C2B: J2.6, U1.5
/C2G: J2.5, U1.4
/C2R: J2.4, U1.3
/C3B: J2.9, U3.15
/C3G: J2.8, U1.7
/C3R: J2.7, U1.6
/C4B: J3.2, U3.3
/C4G: J3.1, U3.2
/C4R: J2.10, U3.1
/C5B: J3.5, U3.6
/C5G: J3.4, U3.5
/C5R: J3.3, U3.4
/C6B: J3.17, U5.1
/C6G: J3.18, U5.15
/C6R: J3.6, U3.7
/C7B: J3.14, U5.2
/C7G: J3.15, U5.3
/C7R: J3.16, U5.4
Button1: J2.12, U2.12
Button2: J2.13, U2.11
Button3: J2.14, U2.6
Button4: J2.15, U2.5
Button5: J2.16, U2.4
Button6: J2.17, U2.3
Button7: J2.18, U2.2
DATA: J1.4, U1.14, U2.17
GND: C1.1, C2.1, C3.2, J1.6, J2.11, J4.2, J5.1, J6.5, U1.8, U2.8, U2.22, U3.8, U4.1, U5.8
unnamed: J5.2, U4.3
unnamed: R1.2, U2.23
unnamed: R2.2, U2.24
unnamed: R3.2, U2.25
unnamed: R4.2, U2.26
unnamed: R5.2, U2.27
unnamed: R6.2, U2.28
unnamed: U1.9, U3.14
unnamed: U3.9, U5.14
RCLK: U1.12, U2.15, U3.12, U5.12
Row1_LEDs: J3.13, R1.1
Row2_LEDs: J3.12, R2.1
Row3_LEDs: J3.11, R3.1
Row4_LEDs: J3.9, R4.1
Row5_LEDs: J3.8, R5.1
Row6_LEDs: J3.7, R6.1
SRCLK: J1.3, U1.11, U2.19, U3.11, U5.11
VCC: C3.1, J1.2, J4.1, J6.1, U1.16, U2.7, U2.20, U2.21, U3.16, U4.2, U5.16
XTAL1: C1.2, U2.9, Y1.1
XTAL2: C2.2, U2.10, Y1.2
~OE: U1.13, U2.16, U3.13, U5.13
~RESET: J1.5, U2.1
~SRCLR: J1.1, U1.10, U2.18, U3.10, U5.10
